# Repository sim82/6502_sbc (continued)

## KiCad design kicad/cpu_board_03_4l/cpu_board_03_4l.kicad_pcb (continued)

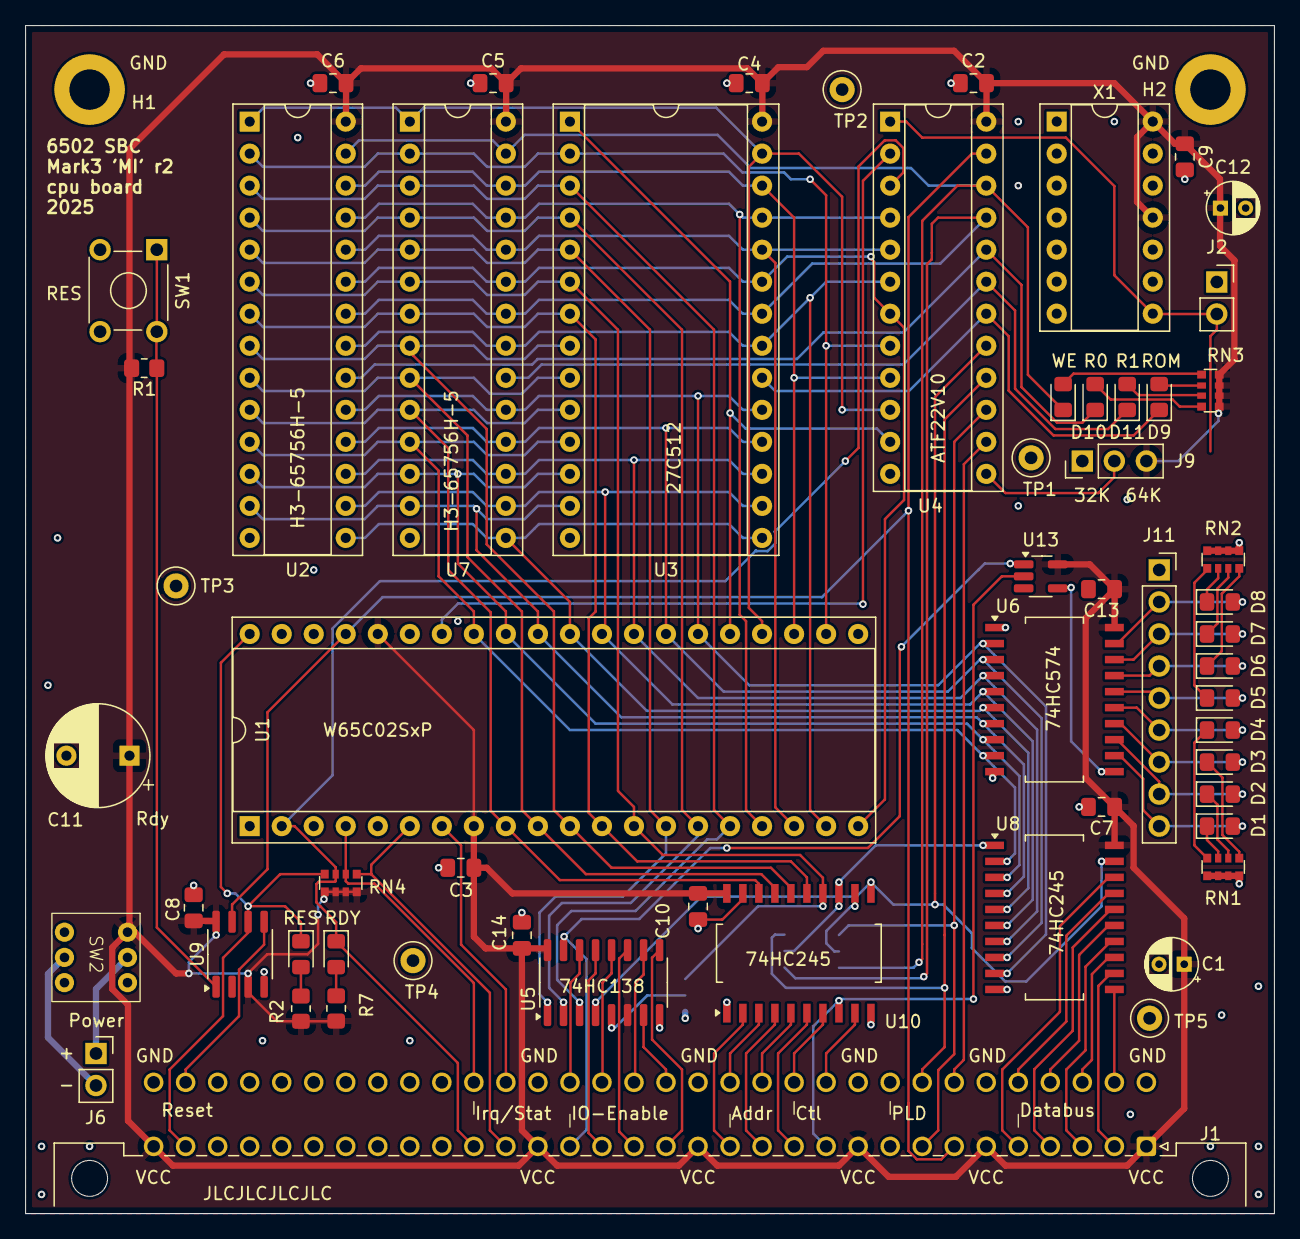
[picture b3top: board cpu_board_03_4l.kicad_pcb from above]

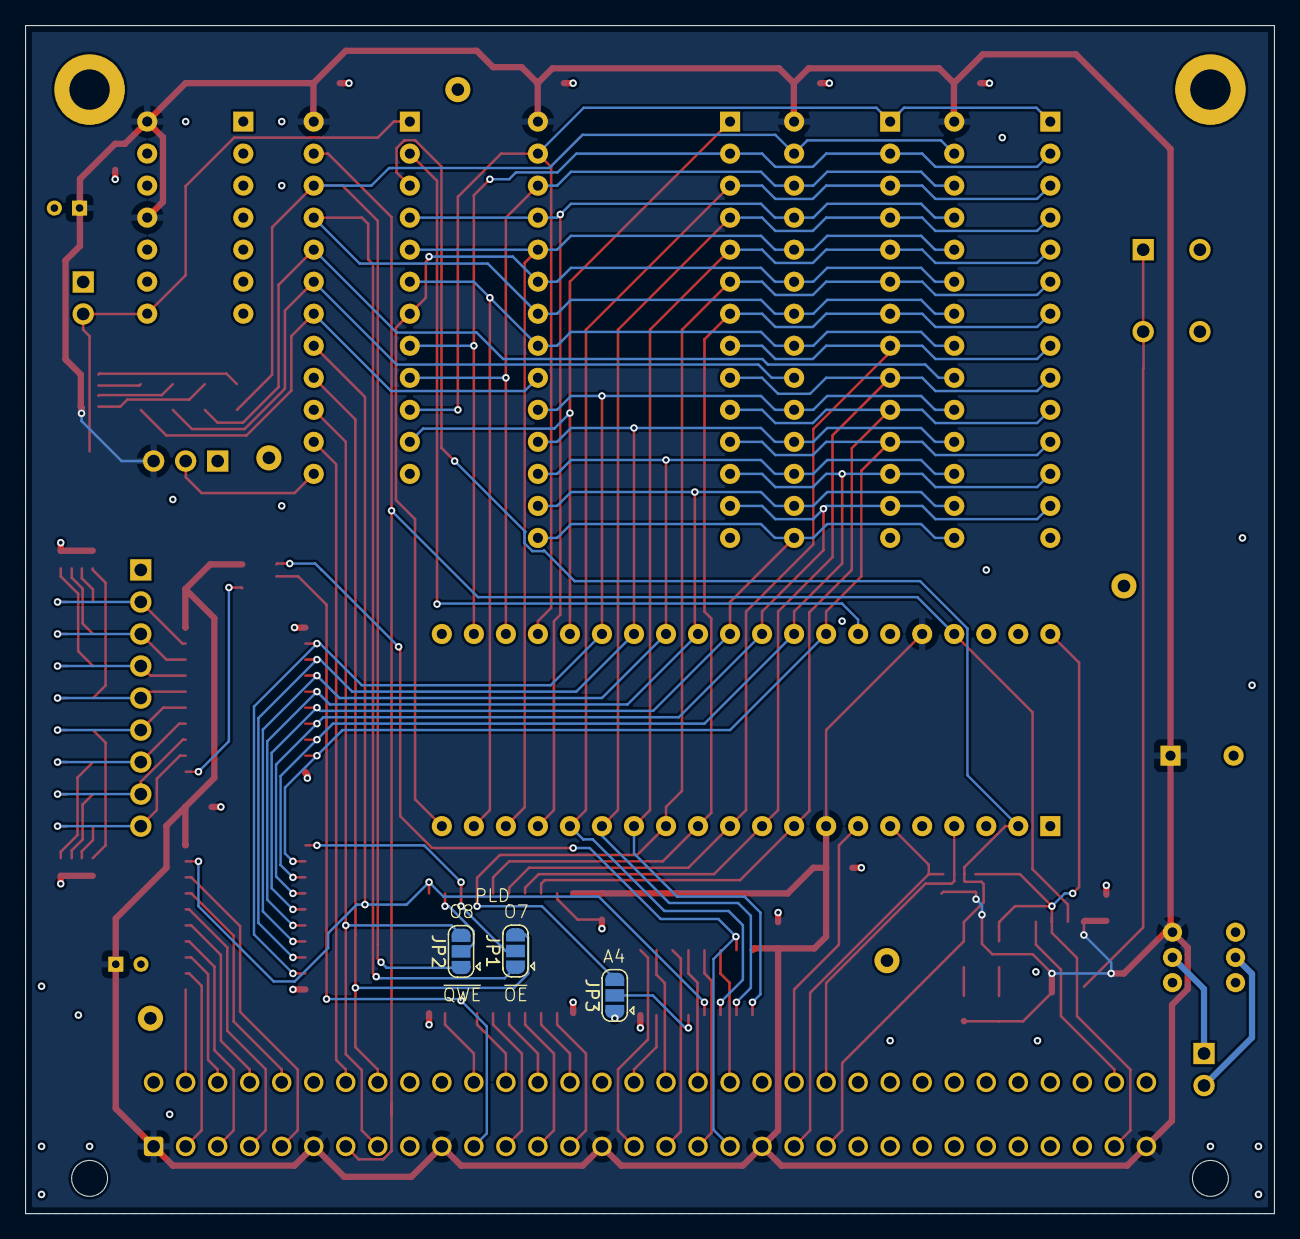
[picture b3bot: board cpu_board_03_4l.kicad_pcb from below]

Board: 4 copper layers, 99.1 x 94.2 mm, 64 parts (3 on the bottom side), 98 nets.

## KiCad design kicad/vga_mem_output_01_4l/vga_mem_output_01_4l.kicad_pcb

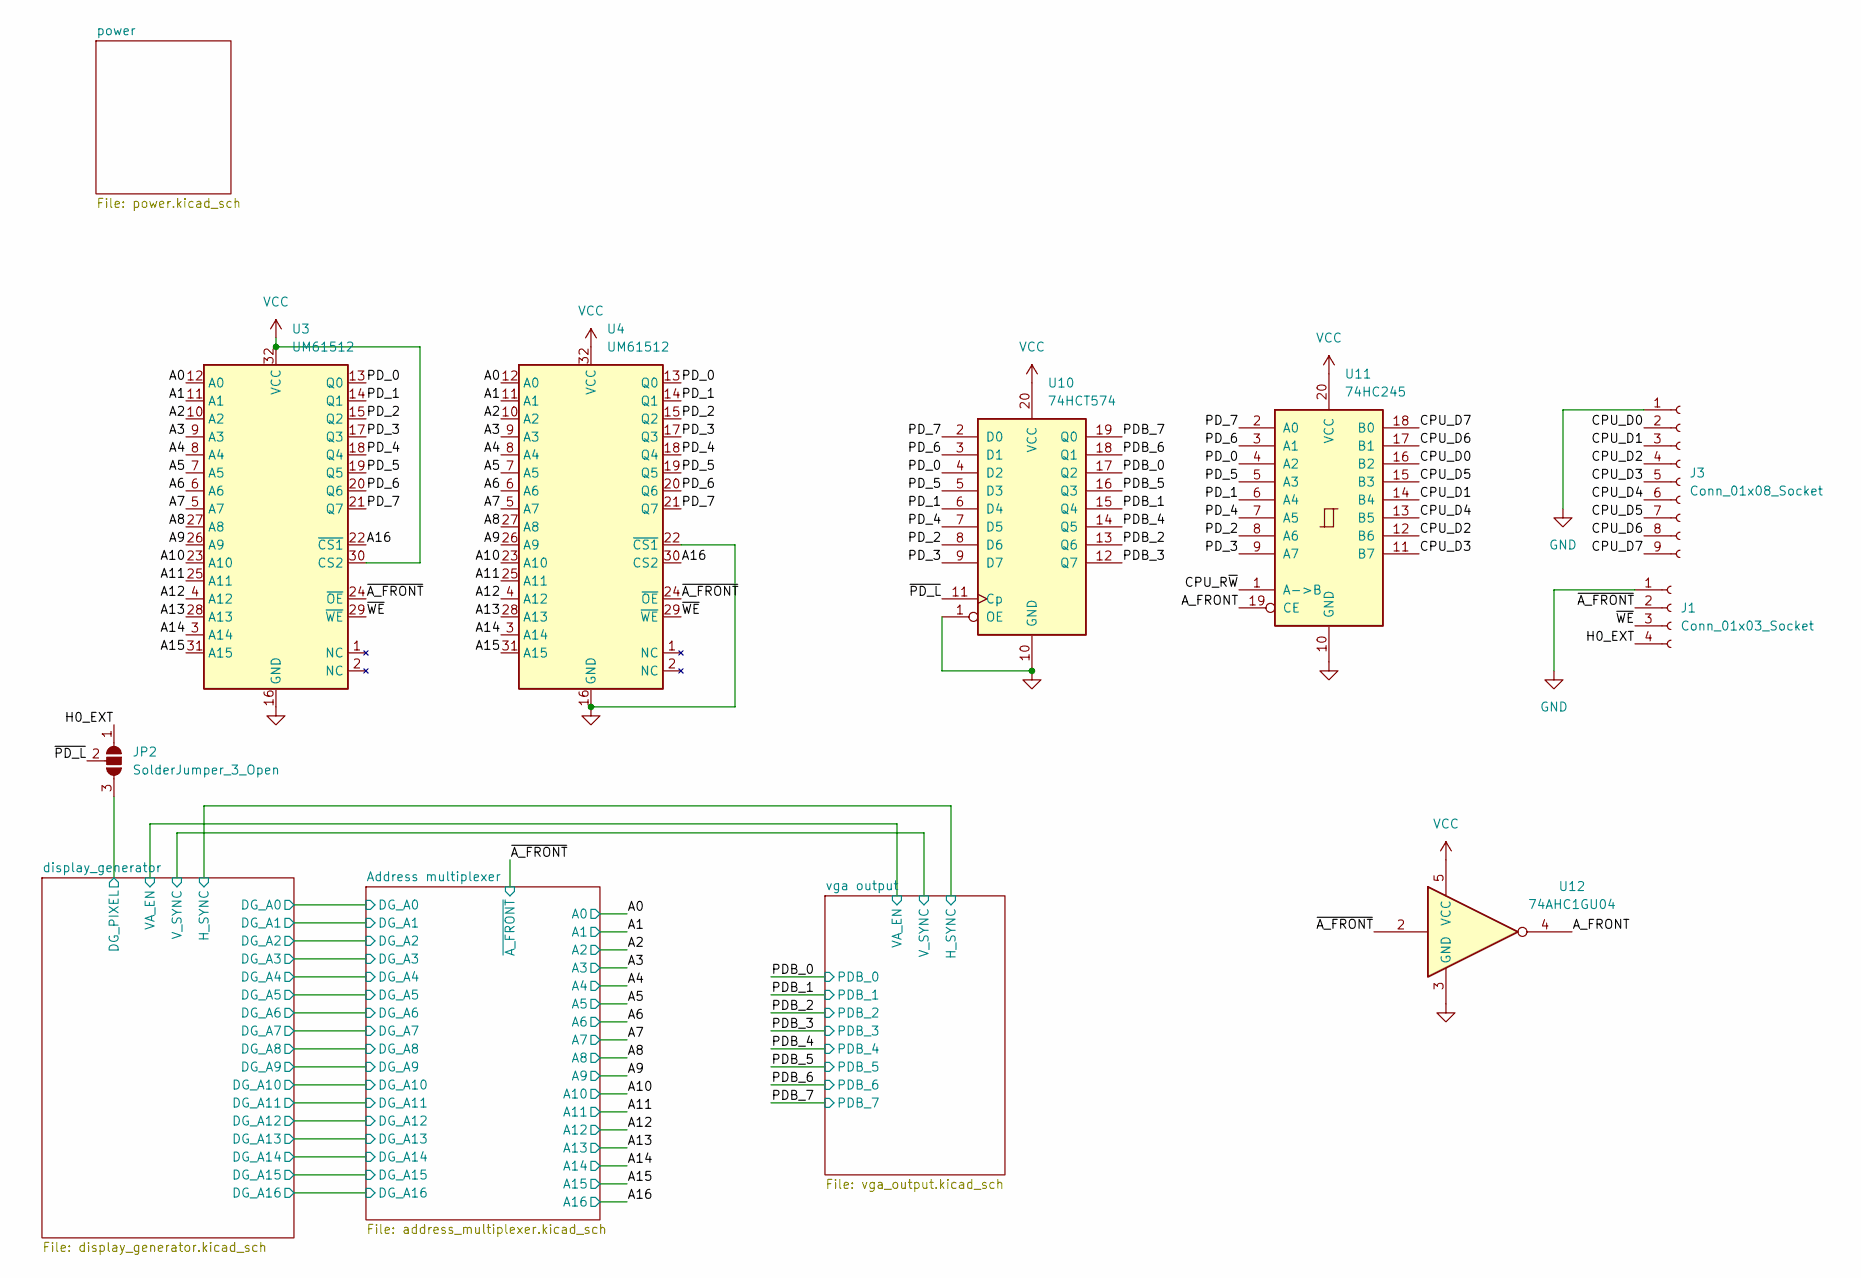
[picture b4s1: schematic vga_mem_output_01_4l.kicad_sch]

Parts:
J1: Conn_01x03_Socket; PinSocket_1x04_P2.54mm_Vertical
J3: Conn_01x08_Socket; PinSocket_1x09_P2.54mm_Vertical
JP2: SolderJumper_3_Open; SolderJumper-3_P1.3mm_Open_RoundedPad1.0x1.5mm
U3, U4: UM61512; DIP-32_W7.62mm
U10: 74HCT574; SO-20_12.8x7.5mm_P1.27mm
U11: 74HC245; SO-20_12.8x7.5mm_P1.27mm
U12: 74AHC1GU04; SOT-23-5_HandSoldering

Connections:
/A0: U3.12 (A0), U4.12 (A0); also elsewhere on the board
/A1: U3.11 (A1), U4.11 (A1); also elsewhere on the board
/A2: U3.10 (A2), U4.10 (A2); also elsewhere on the board
/A3: U3.9 (A3), U4.9 (A3); also elsewhere on the board
/A4: U3.8 (A4), U4.8 (A4); also elsewhere on the board
/A5: U3.7 (A5), U4.7 (A5); also elsewhere on the board
/A6: U3.6 (A6), U4.6 (A6); also elsewhere on the board
/A7: U3.5 (A7), U4.5 (A7); also elsewhere on the board
/A8: U3.27 (A8), U4.27 (A8); also elsewhere on the board
/A9: U3.26 (A9), U4.26 (A9); also elsewhere on the board
/A10: U3.23 (A10), U4.23 (A10); also elsewhere on the board
/A11: U3.25 (A11), U4.25 (A11); also elsewhere on the board
/A12: U3.4 (A12), U4.4 (A12); also elsewhere on the board
/A13: U3.28 (A13), U4.28 (A13); also elsewhere on the board
/A14: U3.3 (A14), U4.3 (A14); also elsewhere on the board
/A15: U3.31 (A15), U4.31 (A15); also elsewhere on the board
/A16: U3.22 (~CS1), U4.30 (CS2); also elsewhere on the board
/A_FRONT: U11.19 (CE), U12.4
/CPU_D0: J3.2, U11.16 (B2)
/CPU_D1: J3.3, U11.14 (B4)
/CPU_D2: J3.4, U11.12 (B6)
/CPU_D3: J3.5, U11.11 (B7)
/CPU_D4: J3.6, U11.13 (B5)
/CPU_D5: J3.7, U11.15 (B3)
/CPU_D6: J3.8, U11.17 (B1)
/CPU_D7: J3.9, U11.18 (B0)
/CPU_R~W: U11.1 (A->B)
/H0_EXT: J1.4, JP2.1 (A)
/PDB_0: U10.17 (Q2); also elsewhere on the board
/PDB_1: U10.15 (Q4); also elsewhere on the board
/PDB_2: U10.13 (Q6); also elsewhere on the board
/PDB_3: U10.12 (Q7); also elsewhere on the board
/PDB_4: U10.14 (Q5); also elsewhere on the board
/PDB_5: U10.16 (Q3); also elsewhere on the board
/PDB_6: U10.18 (Q1); also elsewhere on the board
/PDB_7: U10.19 (Q0); also elsewhere on the board
/PD_0: U3.13 (Q0), U4.13 (Q0), U10.4 (D2), U11.4 (A2)
/PD_1: U3.14 (Q1), U4.14 (Q1), U10.6 (D4), U11.6 (A4)
/PD_2: U3.15 (Q2), U4.15 (Q2), U10.8 (D6), U11.8 (A6)
/PD_3: U3.17 (Q3), U4.17 (Q3), U10.9 (D7), U11.9 (A7)
/PD_4: U3.18 (Q4), U4.18 (Q4), U10.7 (D5), U11.7 (A5)
/PD_5: U3.19 (Q5), U4.19 (Q5), U10.5 (D3), U11.5 (A3)
/PD_6: U3.20 (Q6), U4.20 (Q6), U10.3 (D1), U11.3 (A1)
/PD_7: U3.21 (Q7), U4.21 (Q7), U10.2 (D0), U11.2 (A0)
/display_generator/H0: JP2.3 (B); also elsewhere on the board
/~A_FRONT: J1.2, U3.24 (~OE), U4.24 (~OE), U12.2; also elsewhere on the board
/~PD_L: JP2.2 (C), U10.11 (Cp)
/~WE: J1.3, U3.29 (~WE), U4.29 (~WE)

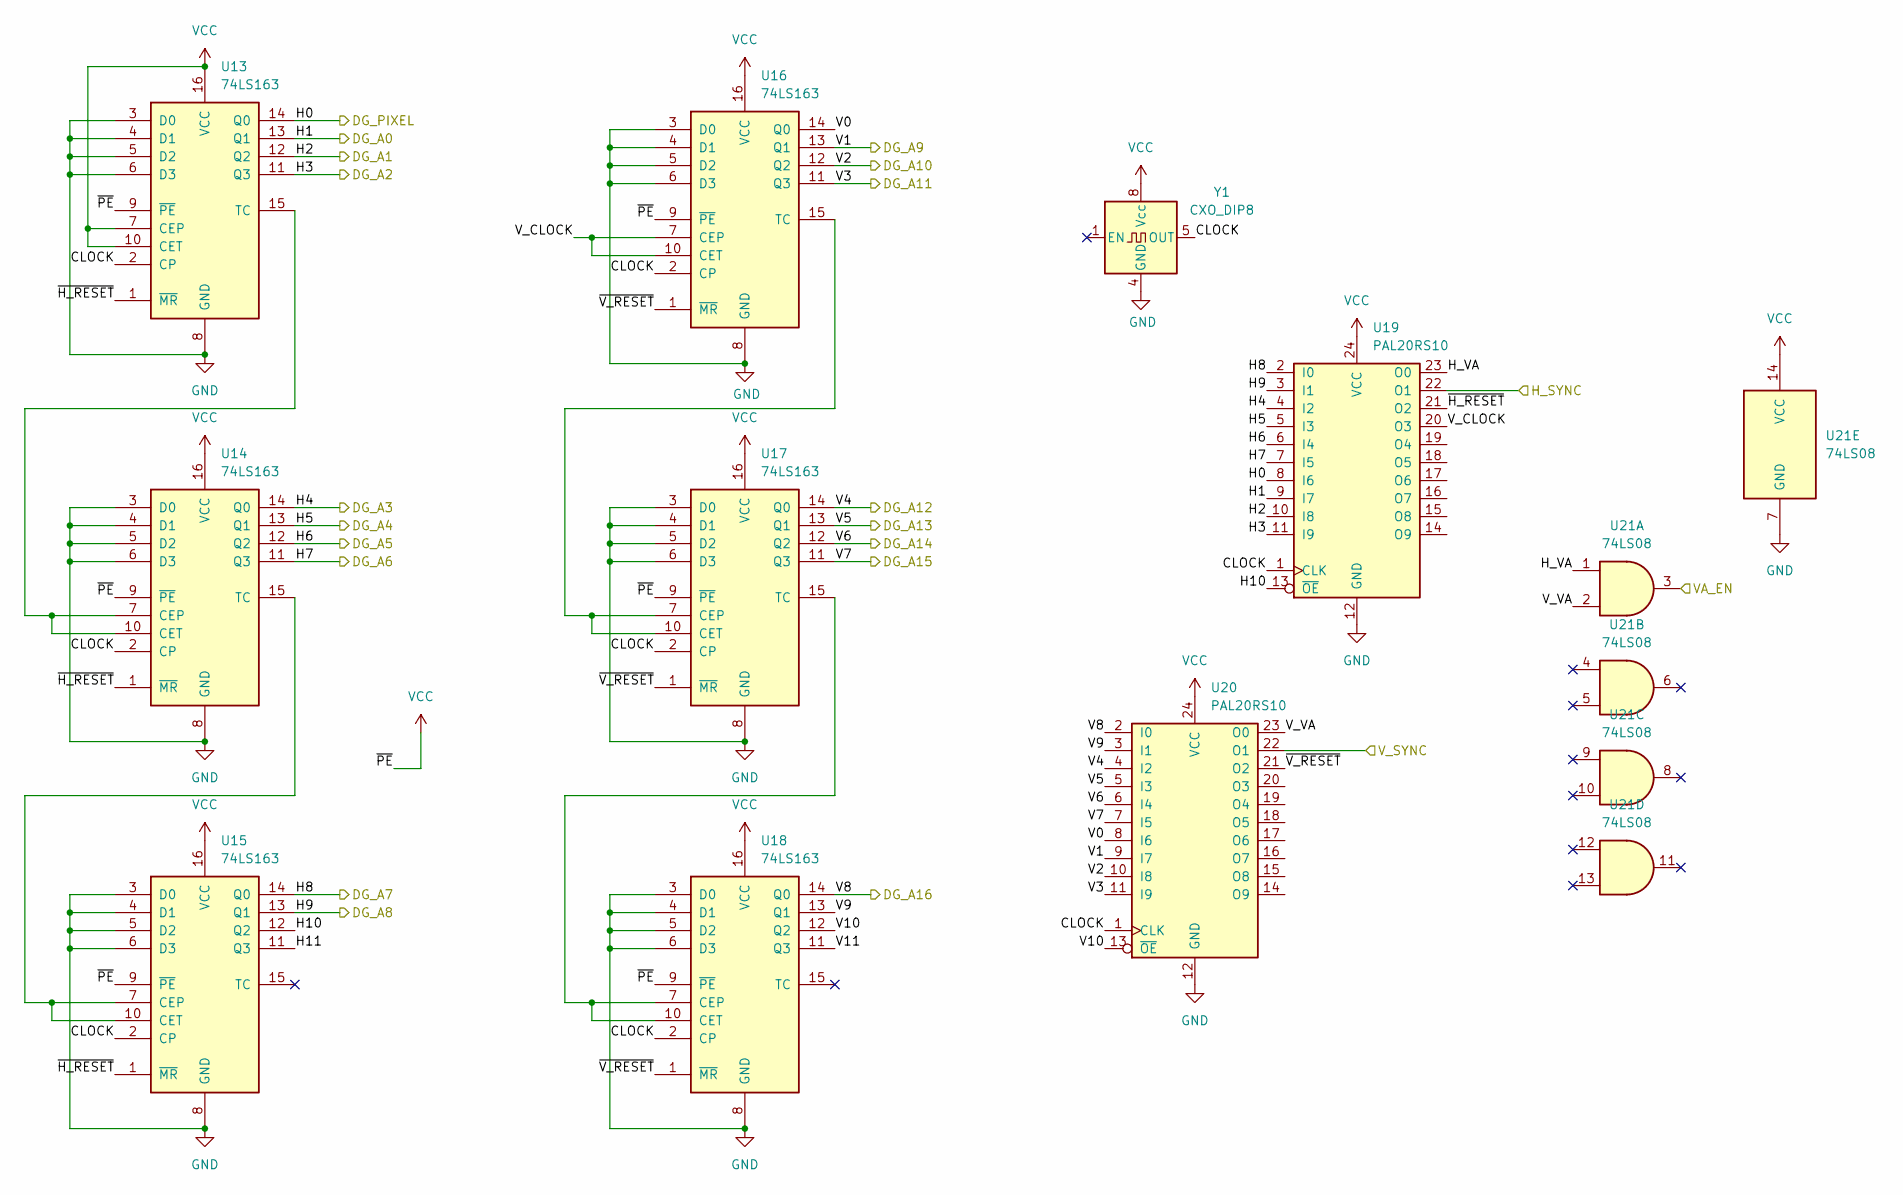
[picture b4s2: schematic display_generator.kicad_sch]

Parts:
U13, U14, U15, U16, U17, U18: 74LS163; SO-16_3.9x9.9mm_P1.27mm
U19, U20: PAL20RS10; DIP-24_W7.62mm_Socket
U21: 74LS08; SO-14_3.9x8.65mm_P1.27mm
Y1: CXO_DIP8; Oscillator_DIP-8

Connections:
/display_generator/CLOCK: U13.2 (CP), U14.2 (CP), U15.2 (CP), U16.2 (CP), U17.2 (CP), U18.2 (CP), U19.1 (CLK), U20.1 (CLK), Y1.5 (OUT)
/display_generator/H0: U13.14 (Q0), U19.8 (I6); also elsewhere on the board
/display_generator/H1: U13.13 (Q1), U19.9 (I7); also elsewhere on the board
/display_generator/H2: U13.12 (Q2), U19.10 (I8); also elsewhere on the board
/display_generator/H3: U13.11 (Q3), U19.11 (I9); also elsewhere on the board
/display_generator/H4: U14.14 (Q0), U19.4 (I2); also elsewhere on the board
/display_generator/H5: U14.13 (Q1), U19.5 (I3); also elsewhere on the board
/display_generator/H6: U14.12 (Q2), U19.6 (I4); also elsewhere on the board
/display_generator/H7: U14.11 (Q3), U19.7 (I5); also elsewhere on the board
/display_generator/H8: U15.14 (Q0), U19.2 (I0); also elsewhere on the board
/display_generator/H9: U15.13 (Q1), U19.3 (I1); also elsewhere on the board
/display_generator/H10: U15.12 (Q2), U19.13 (~OE)
/display_generator/H11: U15.11 (Q3)
/display_generator/H_SYNC: U19.22 (O1); also elsewhere on the board
/display_generator/H_VA: U19.23 (O0), U21.1
/display_generator/V0: U16.14 (Q0), U20.8 (I6)
/display_generator/V1: U16.13 (Q1), U20.9 (I7); also elsewhere on the board
/display_generator/V2: U16.12 (Q2), U20.10 (I8); also elsewhere on the board
/display_generator/V3: U16.11 (Q3), U20.11 (I9); also elsewhere on the board
/display_generator/V4: U17.14 (Q0), U20.4 (I2); also elsewhere on the board
/display_generator/V5: U17.13 (Q1), U20.5 (I3); also elsewhere on the board
/display_generator/V6: U17.12 (Q2), U20.6 (I4); also elsewhere on the board
/display_generator/V7: U17.11 (Q3), U20.7 (I5); also elsewhere on the board
/display_generator/V8: U18.14 (Q0), U20.2 (I0); also elsewhere on the board
/display_generator/V9: U18.13 (Q1), U20.3 (I1)
/display_generator/V10: U18.12 (Q2), U20.13 (~OE)
/display_generator/V11: U18.11 (Q3)
/display_generator/VA_EN: U21.3; also elsewhere on the board
/display_generator/V_CLOCK: U16.7 (CEP), U16.10 (CET), U19.20 (O3)
/display_generator/V_SYNC: U20.22 (O1); also elsewhere on the board
/display_generator/V_VA: U20.23 (O0), U21.2
/display_generator/~H_RESET: U13.1 (~MR), U14.1 (~MR), U15.1 (~MR), U19.21 (O2)
/display_generator/~V_RESET: U16.1 (~MR), U17.1 (~MR), U18.1 (~MR), U20.21 (O2)
unnamed: U13.15 (TC), U14.7 (CEP), U14.10 (CET)
unnamed: U14.15 (TC), U15.7 (CEP), U15.10 (CET)
unnamed: U16.15 (TC), U17.7 (CEP), U17.10 (CET)
unnamed: U17.15 (TC), U18.7 (CEP), U18.10 (CET)

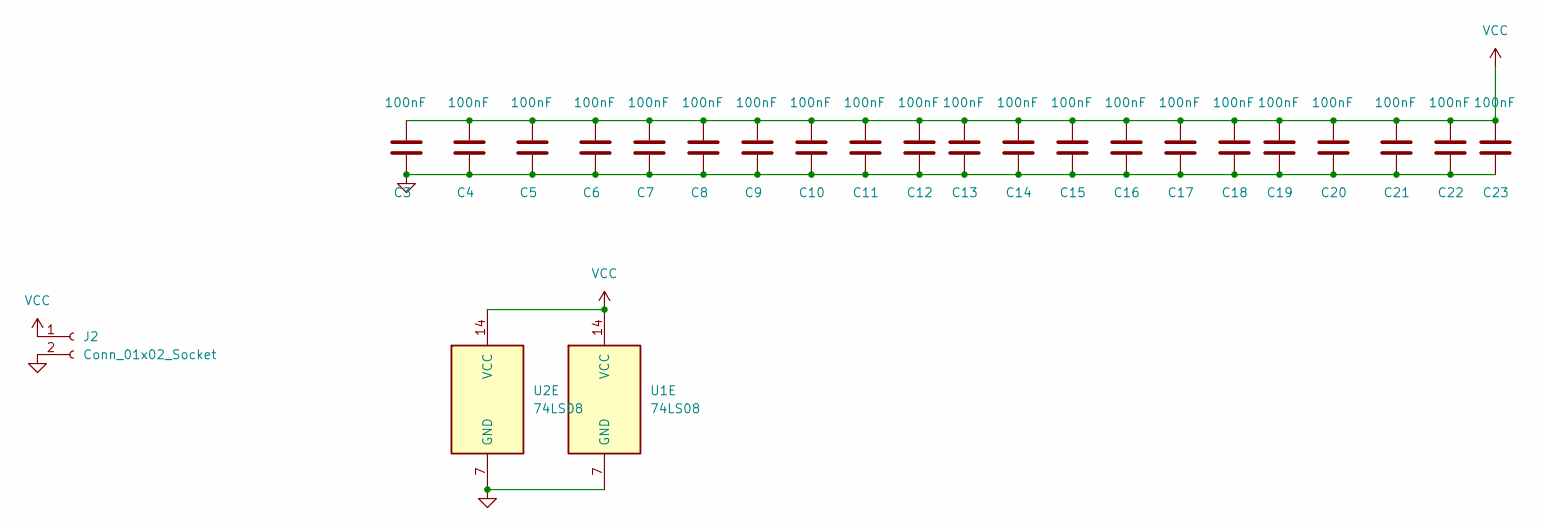
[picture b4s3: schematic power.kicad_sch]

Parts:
C3, C4, C5, C6, C7, C8, C9, C10, C11, C12, C13, C14, C15, C16, C17, C18, C19, C20, C21, C22, C23: 100nF; C_0805_2012Metric_Pad1.18x1.45mm_HandSolder
J2: Conn_01x02_Socket; PinSocket_1x02_P2.54mm_Vertical
U1, U2: 74LS08; SO-14_3.9x8.65mm_P1.27mm

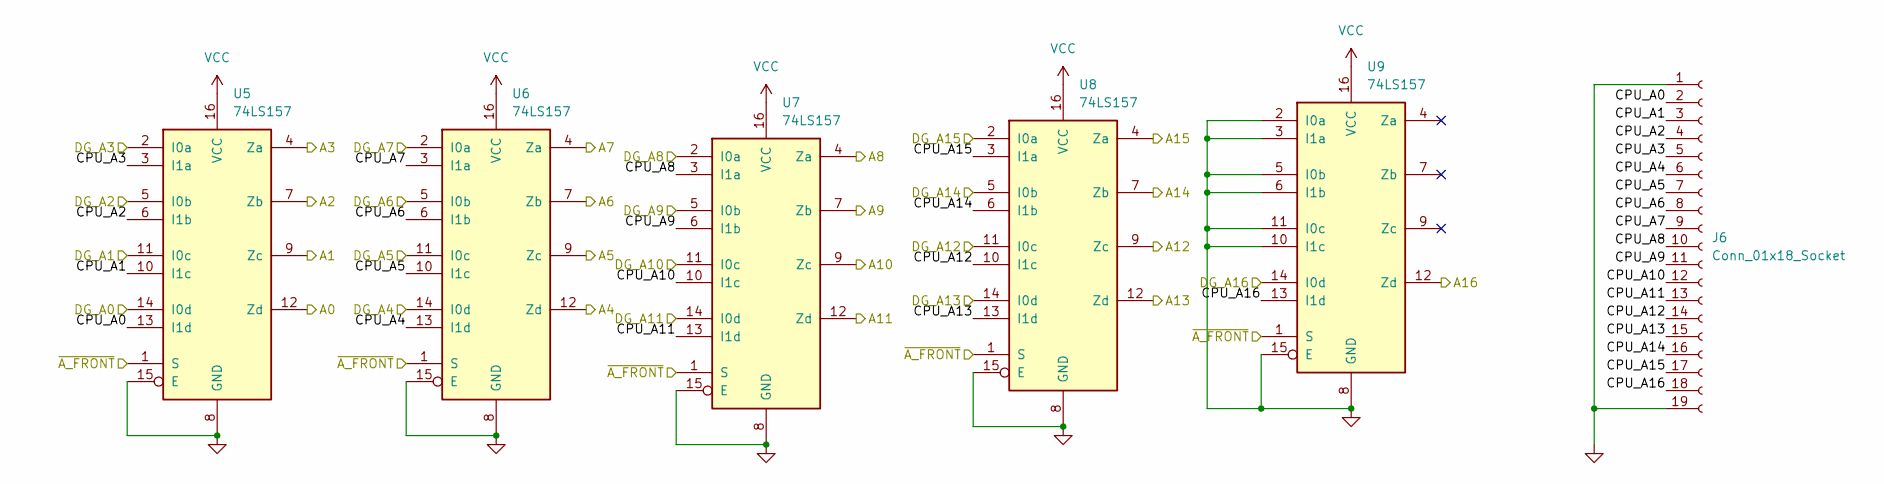
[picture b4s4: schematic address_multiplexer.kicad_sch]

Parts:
J6: Conn_01x18_Socket; PinHeader_1x19_P2.54mm_Vertical
U5, U6, U7, U8, U9: 74LS157; SO-16_3.9x9.9mm_P1.27mm

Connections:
/A0: U5.12 (Zd); also elsewhere on the board
/A1: U5.9 (Zc); also elsewhere on the board
/A2: U5.7 (Zb); also elsewhere on the board
/A3: U5.4 (Za); also elsewhere on the board
/A4: U6.12 (Zd); also elsewhere on the board
/A5: U6.9 (Zc); also elsewhere on the board
/A6: U6.7 (Zb); also elsewhere on the board
/A7: U6.4 (Za); also elsewhere on the board
/A8: U7.4 (Za); also elsewhere on the board
/A9: U7.7 (Zb); also elsewhere on the board
/A10: U7.9 (Zc); also elsewhere on the board
/A11: U7.12 (Zd); also elsewhere on the board
/A12: U8.9 (Zc); also elsewhere on the board
/A13: U8.12 (Zd); also elsewhere on the board
/A14: U8.7 (Zb); also elsewhere on the board
/A15: U8.4 (Za); also elsewhere on the board
/A16: U9.12 (Zd); also elsewhere on the board
/Address multiplexer/CPU_A0: J6.2, U5.13 (I1d)
/Address multiplexer/CPU_A1: J6.3, U5.10 (I1c)
/Address multiplexer/CPU_A2: J6.4, U5.6 (I1b)
/Address multiplexer/CPU_A3: J6.5, U5.3 (I1a)
/Address multiplexer/CPU_A4: J6.6, U6.13 (I1d)
/Address multiplexer/CPU_A5: J6.7, U6.10 (I1c)
/Address multiplexer/CPU_A6: J6.8, U6.6 (I1b)
/Address multiplexer/CPU_A7: J6.9, U6.3 (I1a)
/Address multiplexer/CPU_A8: J6.10, U7.3 (I1a)
/Address multiplexer/CPU_A9: J6.11, U7.6 (I1b)
/Address multiplexer/CPU_A10: J6.12, U7.10 (I1c)
/Address multiplexer/CPU_A11: J6.13, U7.13 (I1d)
/Address multiplexer/CPU_A12: J6.14, U8.10 (I1c)
/Address multiplexer/CPU_A13: J6.15, U8.13 (I1d)
/Address multiplexer/CPU_A14: J6.16, U8.6 (I1b)
/Address multiplexer/CPU_A15: J6.17, U8.3 (I1a)
/Address multiplexer/CPU_A16: J6.18, U9.13 (I1d)
/display_generator/H1: U5.14 (I0d); also elsewhere on the board
/display_generator/H2: U5.11 (I0c); also elsewhere on the board
/display_generator/H3: U5.5 (I0b); also elsewhere on the board
/display_generator/H4: U5.2 (I0a); also elsewhere on the board
/display_generator/H5: U6.14 (I0d); also elsewhere on the board
/display_generator/H6: U6.11 (I0c); also elsewhere on the board
/display_generator/H7: U6.5 (I0b); also elsewhere on the board
/display_generator/H8: U6.2 (I0a); also elsewhere on the board
/display_generator/H9: U7.2 (I0a); also elsewhere on the board
/display_generator/V1: U7.5 (I0b); also elsewhere on the board
/display_generator/V2: U7.11 (I0c); also elsewhere on the board
/display_generator/V3: U7.14 (I0d); also elsewhere on the board
/display_generator/V4: U8.11 (I0c); also elsewhere on the board
/display_generator/V5: U8.14 (I0d); also elsewhere on the board
/display_generator/V6: U8.5 (I0b); also elsewhere on the board
/display_generator/V7: U8.2 (I0a); also elsewhere on the board
/display_generator/V8: U9.14 (I0d); also elsewhere on the board
/~A_FRONT: U5.1 (S), U6.1 (S), U7.1 (S), U8.1 (S), U9.1 (S); also elsewhere on the board

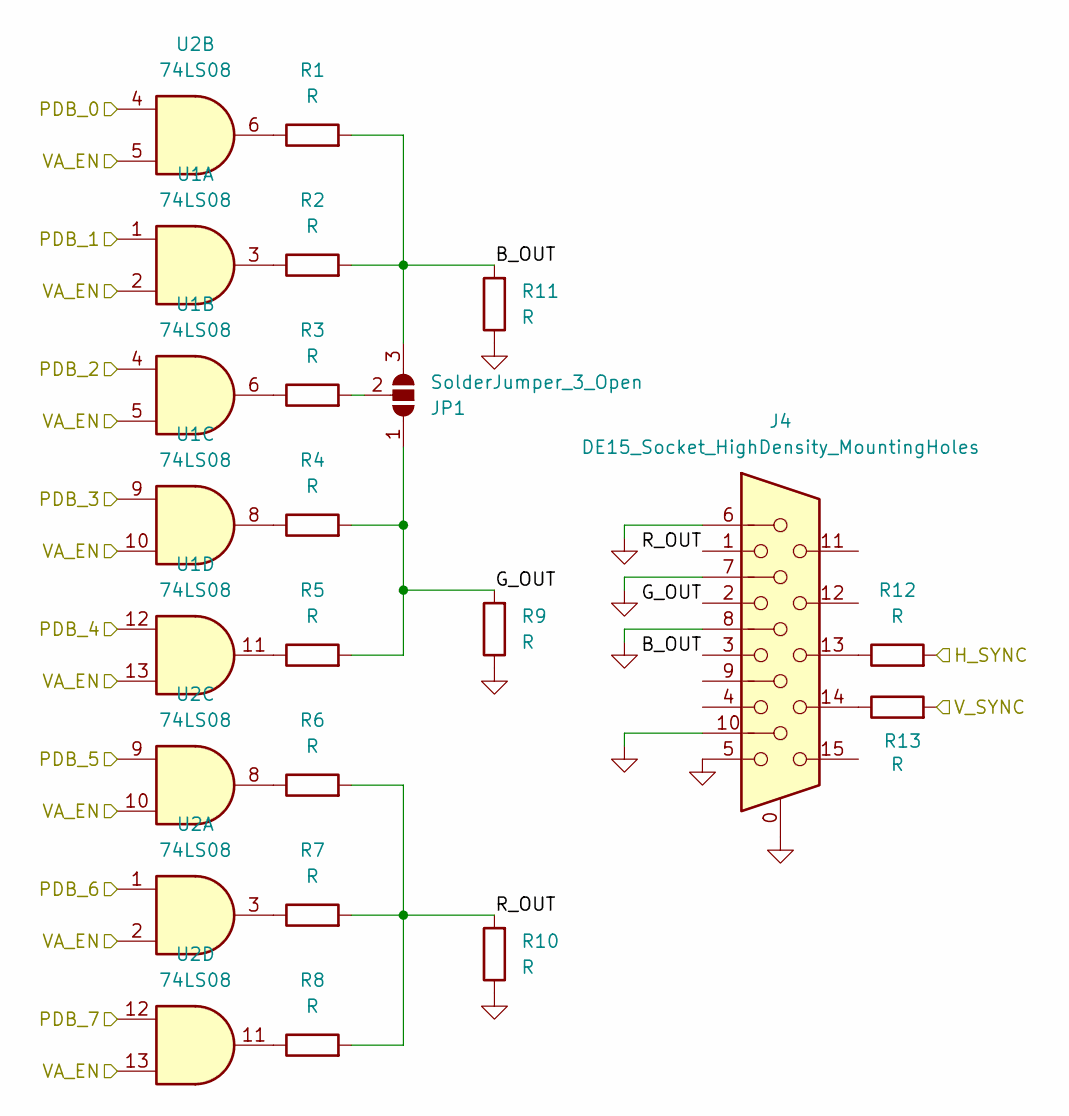
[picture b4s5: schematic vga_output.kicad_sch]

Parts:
J4: DE15_Socket_HighDensity_MountingHoles; DSUB-15-HD_Socket_Horizontal_P2.29x2.54mm_EdgePinOffset8.35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
JP1: SolderJumper_3_Open; SolderJumper-3_P1.3mm_Open_RoundedPad1.0x1.5mm
R1, R2, R3, R4, R5, R6, R7, R8, R9, R10, R11, R12, R13: R; R_Axial_DIN0204_L3.6mm_D1.6mm_P7.62mm_Horizontal
U1, U2: 74LS08; SO-14_3.9x8.65mm_P1.27mm

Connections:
/PDB_0: U2.4; also elsewhere on the board
/PDB_1: U1.1; also elsewhere on the board
/PDB_2: U1.4; also elsewhere on the board
/PDB_3: U1.9; also elsewhere on the board
/PDB_4: U1.12; also elsewhere on the board
/PDB_5: U2.9; also elsewhere on the board
/PDB_6: U2.1; also elsewhere on the board
/PDB_7: U2.12; also elsewhere on the board
/display_generator/H_SYNC: R12.2; also elsewhere on the board
/display_generator/VA_EN: U1.2, U1.5, U1.10, U1.13, U2.2, U2.5, U2.10, U2.13; also elsewhere on the board
/display_generator/V_SYNC: R13.2; also elsewhere on the board
/vga output/B_OUT: J4.3, JP1.3 (B), R1.2, R2.2, R11.2
/vga output/G_OUT: J4.2, JP1.1 (A), R4.2, R5.2, R9.2
/vga output/R_OUT: J4.1, R6.2, R7.2, R8.2, R10.2
unnamed: J4.13, R12.1
unnamed: J4.14, R13.1
unnamed: JP1.2 (C), R3.2
unnamed: R1.1, U2.6
unnamed: R2.1, U1.3
unnamed: R3.1, U1.6
unnamed: R4.1, U1.8
unnamed: R5.1, U1.11
unnamed: R6.1, U2.8
unnamed: R7.1, U2.3
unnamed: R8.1, U2.11

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
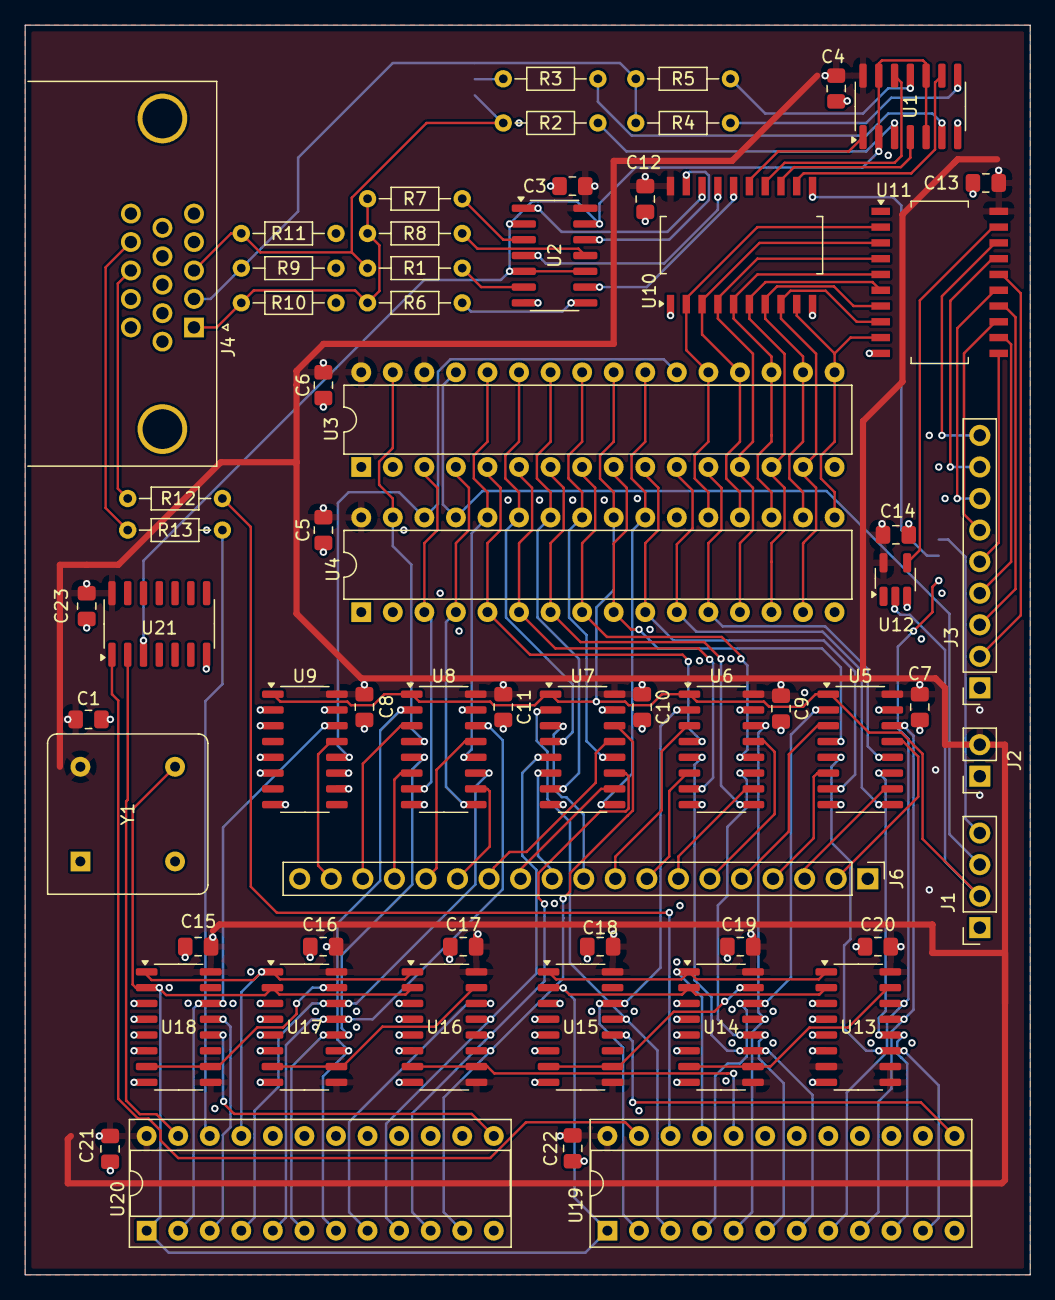
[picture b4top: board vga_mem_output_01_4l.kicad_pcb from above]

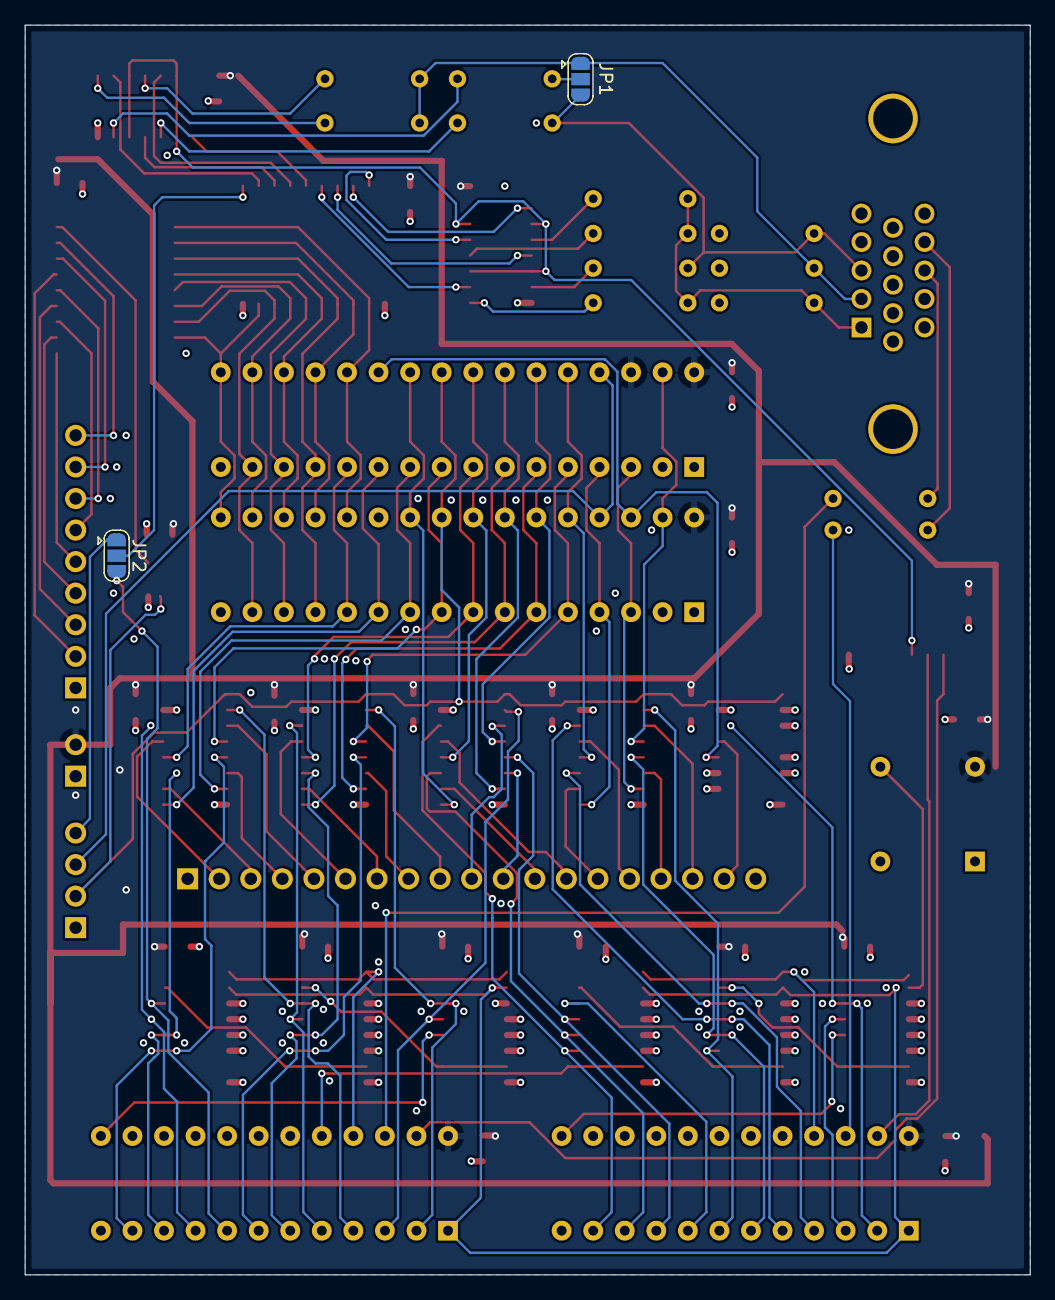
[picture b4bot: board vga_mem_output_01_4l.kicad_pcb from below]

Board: 4 copper layers, 80.9 x 100.6 mm, 64 parts (2 on the bottom side), 114 nets.

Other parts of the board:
C1: 100nF; C_0805_2012Metric_Pad1.18x1.45mm_HandSolder
